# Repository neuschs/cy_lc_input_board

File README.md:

# cy_lc_input_board
Input Protection Board for "Lcsoft CY7C68013A Mini Board"

# Protections

- Input Buffer via 74HC241 or 74HC244 (switchable via Jumper [Output Enables])
- ESD Protection via ESDA6V1L (Didnt choose bigger diode array for signal path reasons) Not necessary but neat.
- Switchable 4,7V Zener Diodes for signals greater than 5V eg 24V. | Series Resistors for current limitation of zener diodes
- Additional USB B port for full enclosure (needs to be hand soldered to the usb footprint of the cypress board)
- External power connector for "expansion" boards. 

# Todo
- Design enclosure
- Add LEDs to the IO header and solder them to the old leds on the cypress board for diagnostic purposes

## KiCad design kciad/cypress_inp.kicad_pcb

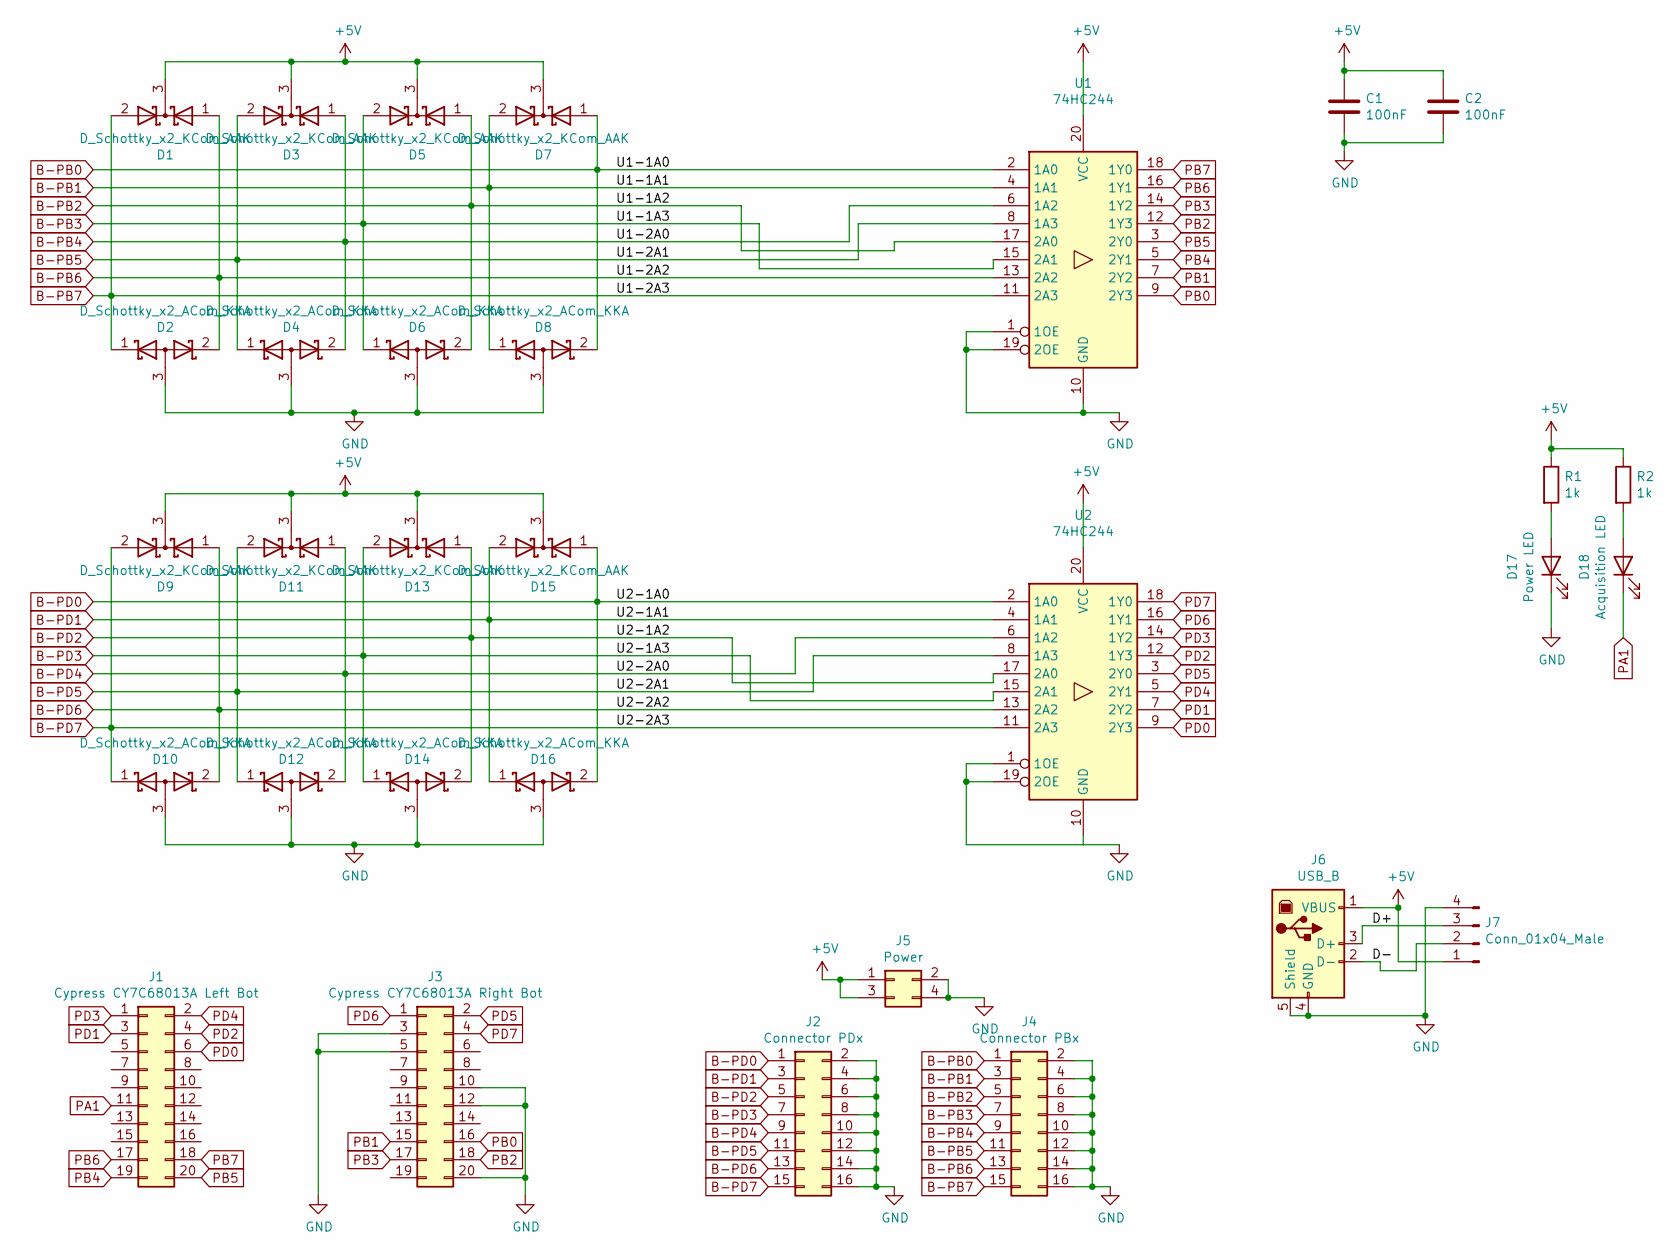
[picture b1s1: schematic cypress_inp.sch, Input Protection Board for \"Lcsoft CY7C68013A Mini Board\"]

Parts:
C1, C2: 100nF; C_1206_3216Metric_Pad1.33x1.80mm_HandSolder
D1, D3, D5, D7, D9, D11, D13, D15: D_Schottky_x2_KCom_AAK; SOT-23_Handsoldering
D2, D4, D6, D8, D10, D12, D14, D16: D_Schottky_x2_ACom_KKA; SOT-23_Handsoldering
D17: Power LED; LED_D3.0mm
D18: Acquisition LED; LED_D3.0mm
J1: Cypress CY7C68013A Left Bot; PinSocket_2x10_P2.54mm_Vertical
J2: Connector PDx; PinSocket_2x08_P2.54mm_Horizontal
J3: Cypress CY7C68013A Right Bot; PinSocket_2x10_P2.54mm_Vertical
J4: Connector PBx; PinSocket_2x08_P2.54mm_Horizontal
J5: Power; PinSocket_2x02_P2.54mm_Horizontal
J6: USB_B; USB_B_TE_5787834_Vertical
J7: Conn_01x04_Male; PinHeader_1x04_P2.54mm_Vertical
R1, R2: 1k; R_1210_3225Metric_Pad1.30x2.65mm_HandSolder
U1, U2: 74HC244; SO-20_5.3x12.6mm_P1.27mm

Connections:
+5V: C1.1, C2.1, D1.3 (K), D3.3 (K), D5.3 (K), D7.3 (K), D9.3 (K), D11.3 (K), D13.3 (K), D15.3 (K), J5.1, J5.3, J6.1 (VBUS), J7.1, R1.1, R2.1, U1.20 (VCC), U2.20 (VCC)
/D+: J6.3 (D+), J7.3
/D-: J6.2 (D-), J7.2
B-PB0: D7.1 (A), D8.2 (K), J4.1, U1.2 (1A0)
B-PB1: D7.2 (A), D8.1 (K), J4.3, U1.4 (1A1)
B-PB2: D5.1 (A), D6.2 (K), J4.5, U1.17 (2A0)
B-PB3: D5.2 (A), D6.1 (K), J4.7, U1.15 (2A1)
B-PB4: D3.1 (A), D4.2 (K), J4.9, U1.6 (1A2)
B-PB5: D3.2 (A), D4.1 (K), J4.11, U1.8 (1A3)
B-PB6: D1.1 (A), D2.2 (K), J4.13, U1.13 (2A2)
B-PB7: D1.2 (A), D2.1 (K), J4.15, U1.11 (2A3)
B-PD0: D15.1 (A), D16.2 (K), J2.1, U2.2 (1A0)
B-PD1: D15.2 (A), D16.1 (K), J2.3, U2.4 (1A1)
B-PD2: D13.1 (A), D14.2 (K), J2.5, U2.17 (2A0)
B-PD3: D13.2 (A), D14.1 (K), J2.7, U2.15 (2A1)
B-PD4: D11.1 (A), D12.2 (K), J2.9, U2.6 (1A2)
B-PD5: D11.2 (A), D12.1 (K), J2.11, U2.8 (1A3)
B-PD6: D9.1 (A), D10.2 (K), J2.13, U2.13 (2A2)
B-PD7: D9.2 (A), D10.1 (K), J2.15, U2.11 (2A3)
GND: C1.2, C2.2, D2.3 (A), D4.3 (A), D6.3 (A), D8.3 (A), D10.3 (A), D12.3 (A), D14.3 (A), D16.3 (A), D17.1 (K), J2.2, J2.4, J2.6, J2.8, J2.10, J2.12, J2.14, J2.16, J3.3, J3.5, J3.10, J3.12, J3.20, J4.2, J4.4, J4.6, J4.8, J4.10, J4.12, J4.14, J4.16, J5.2, J5.4, J6.4 (GND), J6.5 (Shield), J7.4, U1.1 (1OE), U1.10 (GND), U1.19 (2OE), U2.1 (1OE), U2.10 (GND), U2.19 (2OE)
unnamed: D17.2 (A), R1.2
unnamed: D18.2 (A), R2.2
PA1: D18.1 (K), J1.11
PB0: J3.16, U1.9 (2Y3)
PB1: J3.15, U1.7 (2Y2)
PB2: J3.18, U1.12 (1Y3)
PB3: J3.17, U1.14 (1Y2)
PB4: J1.19, U1.5 (2Y1)
PB5: J1.20, U1.3 (2Y0)
PB6: J1.17, U1.16 (1Y1)
PB7: J1.18, U1.18 (1Y0)
PD0: J1.6, U2.9 (2Y3)
PD1: J1.3, U2.7 (2Y2)
PD2: J1.4, U2.12 (1Y3)
PD3: J1.1, U2.14 (1Y2)
PD4: J1.2, U2.5 (2Y1)
PD5: J3.2, U2.3 (2Y0)
PD6: J3.1, U2.16 (1Y1)
PD7: J3.4, U2.18 (1Y0)

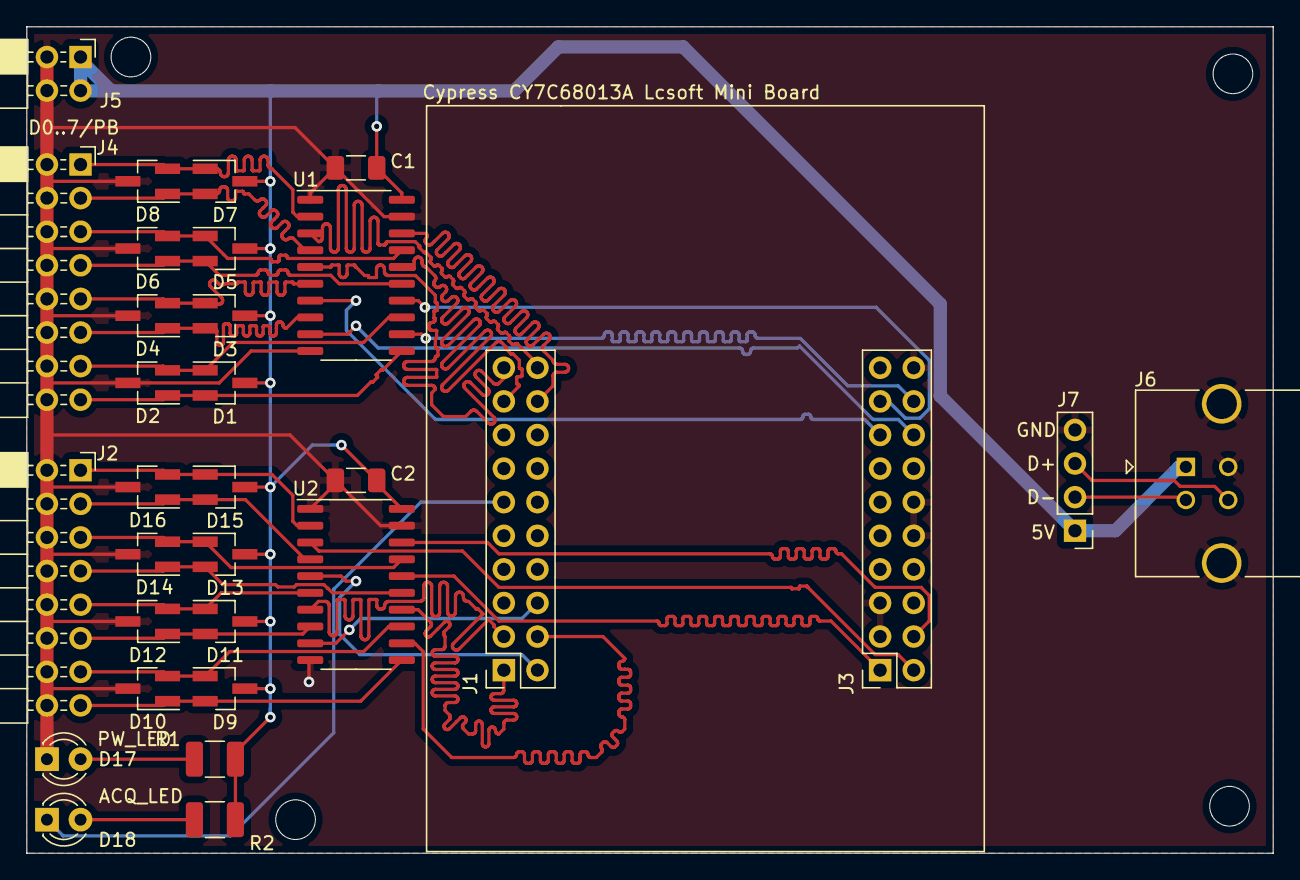
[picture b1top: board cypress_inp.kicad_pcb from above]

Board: 2 copper layers, 94.2 x 62.5 mm, 31 parts (0 on the bottom side), 39 nets.

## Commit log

2021-06-20 * initial commit, pcb is almost done
2021-06-22 * changed layout so signal paths are shorter
2021-06-23 * changed whole schematic and pcb layout
2021-06-24 * added gerber files, * copleted routing of pcb
